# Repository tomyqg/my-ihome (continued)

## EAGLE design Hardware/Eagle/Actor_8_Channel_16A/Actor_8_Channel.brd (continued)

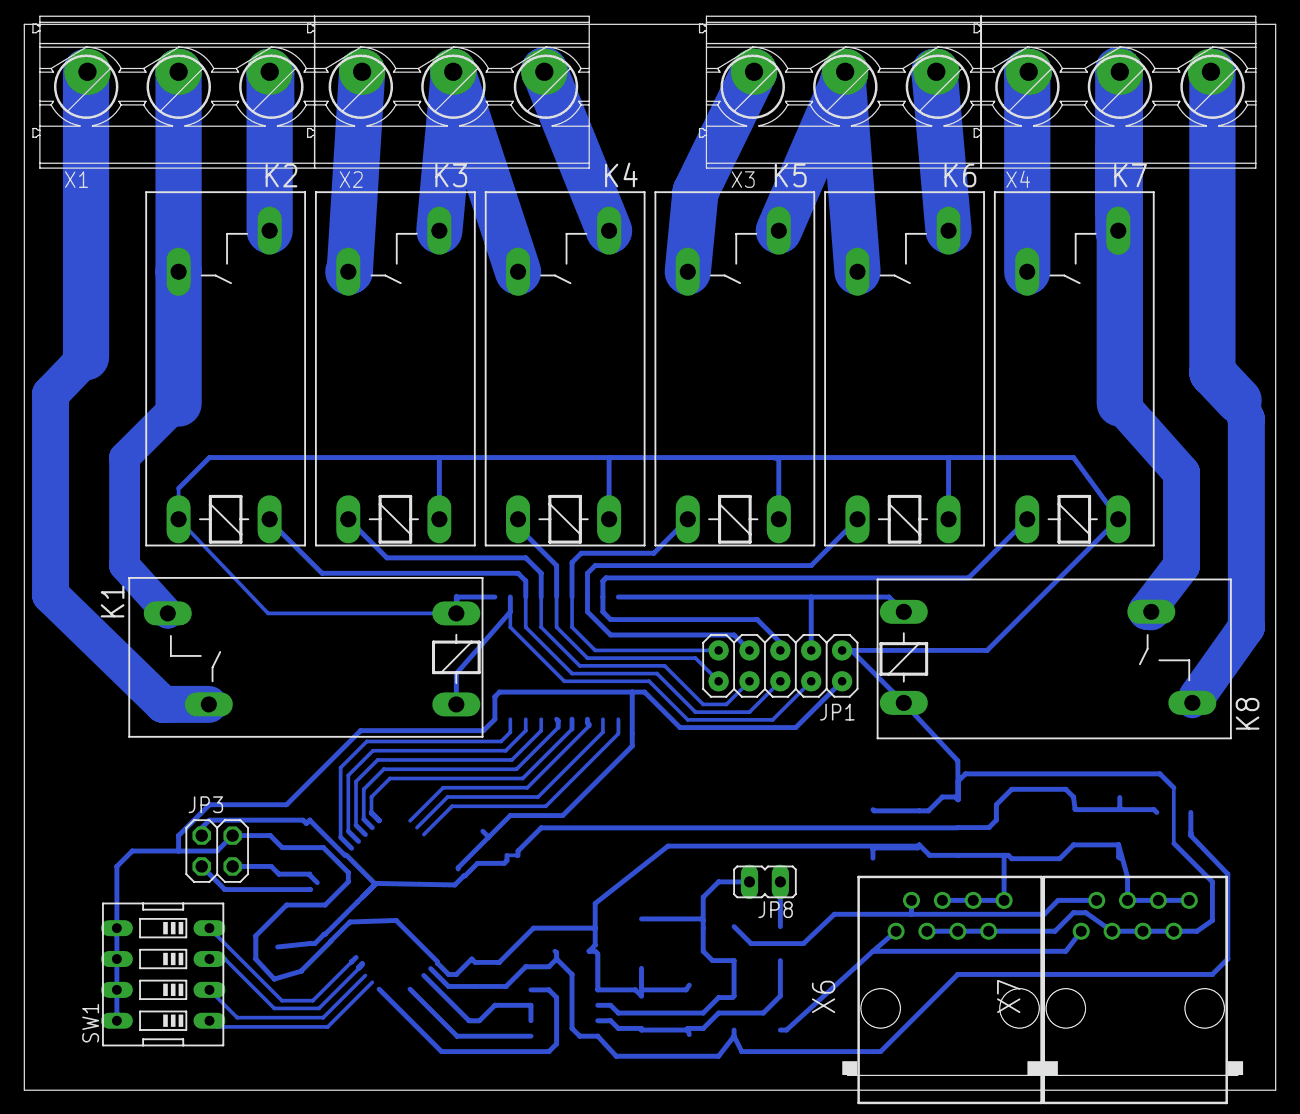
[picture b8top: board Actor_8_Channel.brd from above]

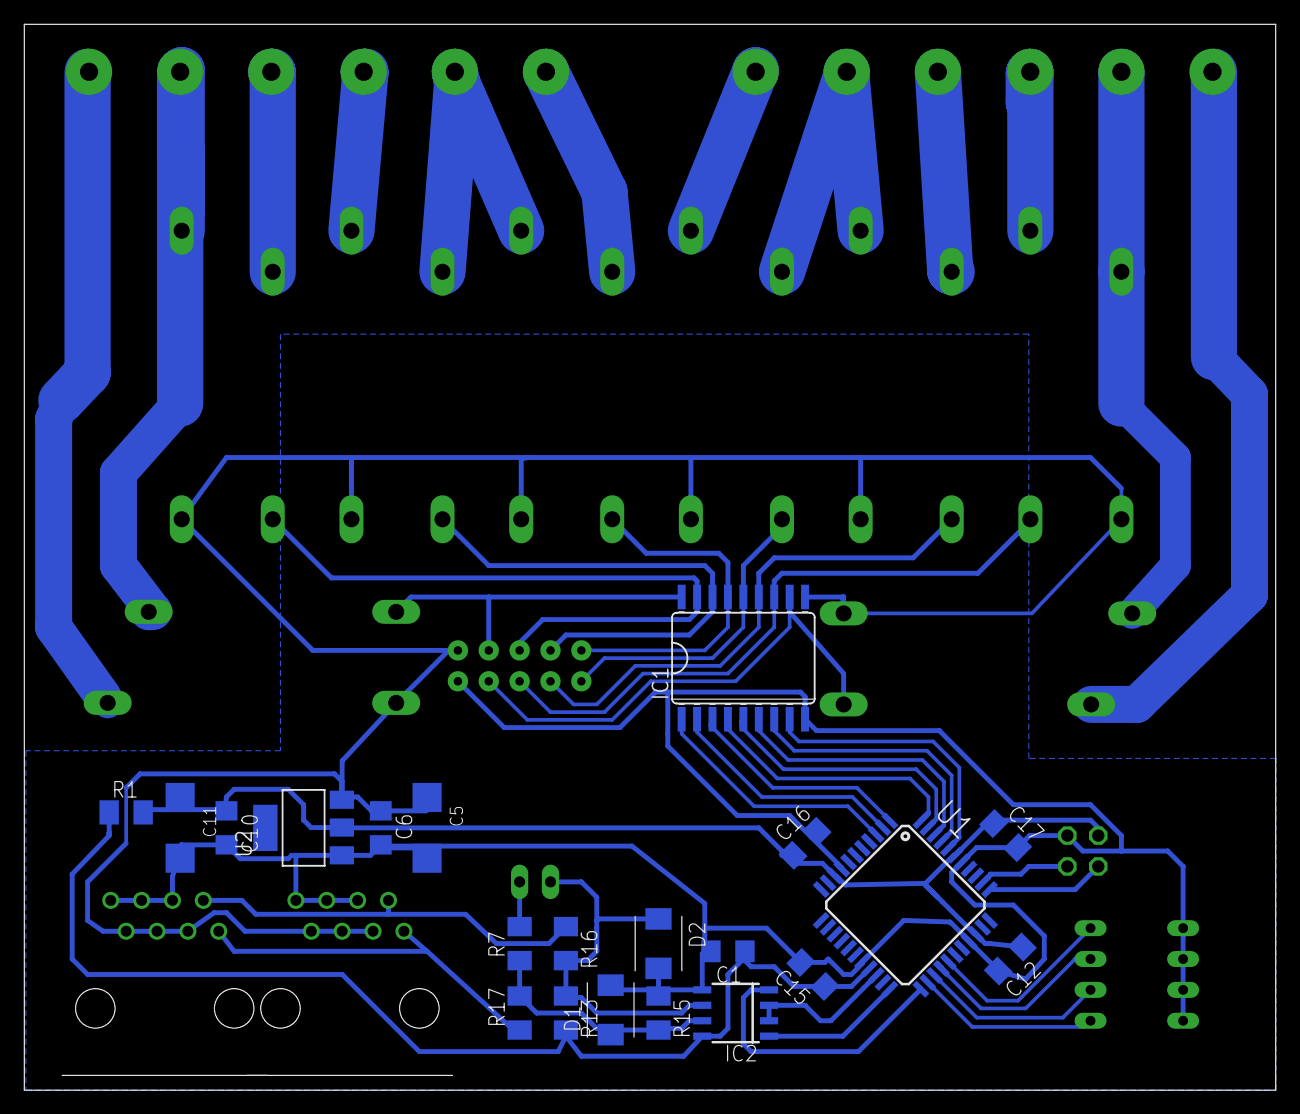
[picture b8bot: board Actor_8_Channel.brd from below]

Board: 2 copper layers, 103.0 x 87.7 mm, 39 parts (21 on the bottom side), 45 nets.

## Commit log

2013-01-30 AtmelStudio 6 solution - initial version.
2013-01-30 Board configuration file. Initial version. Actor8CH config currently used.
2013-01-30 CRC driver implementation copied from ASF 3.5.1.
2013-01-30 CRC driver implementation header copied from ASF 3.5.1.
2013-01-30 FIFO implementation copied from ASF 3.5.1.
2013-01-30 FIFO implementation header file copied from ASF 3.5.1.
2013-01-30 Non-Volatile Memory driver implementation. Initial version.
2013-01-30 Non-Volatile Memory driver implementation header. Initial version.
2013-01-30 Timer/Counter driver.
2013-01-30 USART driver header file. Initial version.
2013-01-30 USART driver implementation file. Initial version.
2013-01-30 Utilities. NOP and memory barrier implementation.
2013-01-30 Multi master network master file. Initial version. Functionality already tested: 1. Main loop based on events handling. 2. CRC - hardware, software and copied from ASF 3.5.1. 3. Timers - busy line, n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
2013-01-30 VisualStudio project file.
2013-01-31 Serial Multi-Master Network State Machine header file. Initial version. Not teste
2013-01-31 Serial Multi-Master Network State Machine implementation. Initial version. Not tested.
2013-02-01 Description added.
2013-02-01 Event refinement. Bug fixed.
2013-02-01 Timer restart added.
2013-02-01 Clock configuration function added. Event changed to FSM-like.
2013-02-17 work in progress
2013-02-17 Communication USART added.
2013-02-17 work in progress...
2013-02-19 type definition added.
2013-02-21 Setter and Getters for frame added.
2013-02-21 temp.
2013-02-21 testing.
2013-02-24 Initial version.
2013-03-04 Warnings as errors turned on.
2013-03-04 Function for CRC-16 hardware calculation added. ADC based random generation added. SRAM content based random generation added.
2013-03-04 Prototypes added. Bit manipulation macros added.
2013-03-06 Timer definitions updated to use common prescaler everywhere.
2013-03-06 XMEGA clock management added.
2013-03-06 Helper functions added.
2013-03-06 Clean-up. Moving utilities to external files. Work in progress.
2013-03-07 draft for all family front touch panel
2013-03-10 Collision Avoidance timer definition added.
2013-03-10 Minor documentation change.
2013-03-10 Communication handling added.
2013-03-10 Command Desciptor Table added.
2013-03-10 Initialization part changed. Timer renamed.
2013-03-10 Eagle project initial pack
2013-03-14 work in progress.. no change
2013-03-15 Atmel XMEGA-A3BU Xplained Hardware User Guide with light sensor.
2013-03-16 FLAG_SET macro added.
2013-03-16 Multi-master Serial Network debug define added.
2013-03-16 Error handling added.
2013-03-16 Error handling added. Cleanup. Data receiving stream tweaked. Command Execution handler supplemented.
2013-03-16 Logical network address functionality tested. Debug added.
2013-03-20 Data Frame
2013-03-21 Base tables version for discussion.
2013-03-22 View of Touch Panel after rescale and added drill hole
2013-03-22 Latest Touch Panel version after rescale (82 mm hight), added drill hole and other suggestion :)
2013-03-24 Initial version of Receiver Finite State Machine.
2013-03-24 Small changes. Refactoring.
2013-03-24 Small changes. Refactoring. Receiver FSM include added.
2013-03-24 Further development - mainly Sending stream.
2013-03-24 New files added (Receiver FSM).
2013-03-26 Family Touch Panel Final Version (FV). Black. Added montage proposal.
2013-03-26 Minor changes
2013-03-26 Modulbox dimensions (6M type for Actor 8 Channel)
2013-03-26 Layout Touch Panel Final Version (FV). Black. Added montage proposal.
2013-03-27 Current Measure Base Info
2013-04-02 INA199A1-A3 evaluation module
2013-04-02 Analog Output Current Shunt and Voltage Instantaneous Power Monitor
2013-04-02 Dimmer base info
2013-04-03 Touch Panel initial information
2013-04-03 Current Measure Test Board
2013-04-03 Initial Version
2013-04-03 16-bit SIPO constant-current LED driver datasheet
2013-04-03 SCT2024 typical application
2013-04-05 Minor changes. Led reduced&resized
2013-04-08 sth 2do 4u
2013-04-08 Touch Pad Board (PCB A) initial version
2013-04-11 Board of TPB (PCB A) - :)Done
2013-04-12 photo transistor used at Touch Panel
2013-04-16 Touch Panel PCB_A & PCB_B final version (to electrical&part check)
2013-04-18 RS-485 driver definition added.
2013-04-18 Serial number related code moved into this file.
2013-04-18 Serial number related code moved into this module. USART configuration function moved into this module.
2013-04-18 Massive rework. Receiving side tested in real testing environment.
2013-04-22 Test Board Update
2013-04-22 Touch Panel (PCBA+PCBB) ver. 1.00
2013-04-23 System tree draft.
2013-05-10 New macros for sending attributes added. Further Sending development.
2013-05-10 Small improvements.
2013-05-10 Further Sending development.
2013-05-13 Atmel's Documentation of power meter (schematics & code)
2013-05-13 Zero Cross Detector
2013-05-16 Single-Phase Multifunction Metering
2013-05-27 Initial sending.
2013-05-27 Touch Panel Qmatrix pin config
2013-05-28 Current, Voltage & Power Meter up to 26VDC
2013-05-28 Power Meter info
2013-05-29 Touch Panel Cases
2013-05-31 Receiving data structure changed to handle endianess more smoothly.
2013-05-31 Changes due to receiving structure improvement (endianess).
2013-05-31 Changes related to receiving data structure change (endianess AVR vs network).
2013-05-31 PDI signals renamed.
2013-06-01 From forum.
2013-06-15 Touch Panel @acad
2013-06-15 Touch Panel @ raster (pdf,png,tif)
2013-06-20 Actor 6 Channel 16A review ver.
2013-06-20 Actor 6CH_PM (Power Measure)
2013-07-03 Info about power metering
2013-07-03 Materials regarding Communication added. RS-485 specific materials added. AVT Project added.
2013-07-06 OneWire driver DS18B20 sensor
2013-07-08 Actor 6CH for review
2013-07-10 Power Measure Test Board for review
2013-07-15 Actor_6_Channel.brd FV
2013-07-17 BOM of A6CH_16A
2013-07-26 F_CPU changed to 8MHz
2013-07-27 Multi-Master Serial Network Protocol. First drop-off after prototyping on A8CH (16AU).
2013-08-04 Multi-Master Serial Network Protocol. Tested with Touch Panel v1.0.
2013-08-04 NVM driver
2013-08-04 USART driver
2013-08-04 fifo, utils
2013-08-04 TimerCounter driver
2013-08-06 Initial version of MMSNP common definitions.
2013-08-06 Array with delay times for Actor_8.
2013-08-07 small rework
2013-08-07 Small rework.
2013-08-14 Changes after system tests in the building.
2013-08-18 Interrupt setting fixed.
2013-08-18 Code beatify.
2013-08-18 Debug macro added. New comments added.
2013-08-18 Fixes after system tests in the building.
2013-08-19 xmega_software_reset() function added.
2013-08-21 define for CRC-16 computation method added.
2013-08-21 define for CRC-16 computation method added. Xmega software reset function added.
2013-08-21 Association types added.
2016-01-15 Migrating wiki contents from Google Code
